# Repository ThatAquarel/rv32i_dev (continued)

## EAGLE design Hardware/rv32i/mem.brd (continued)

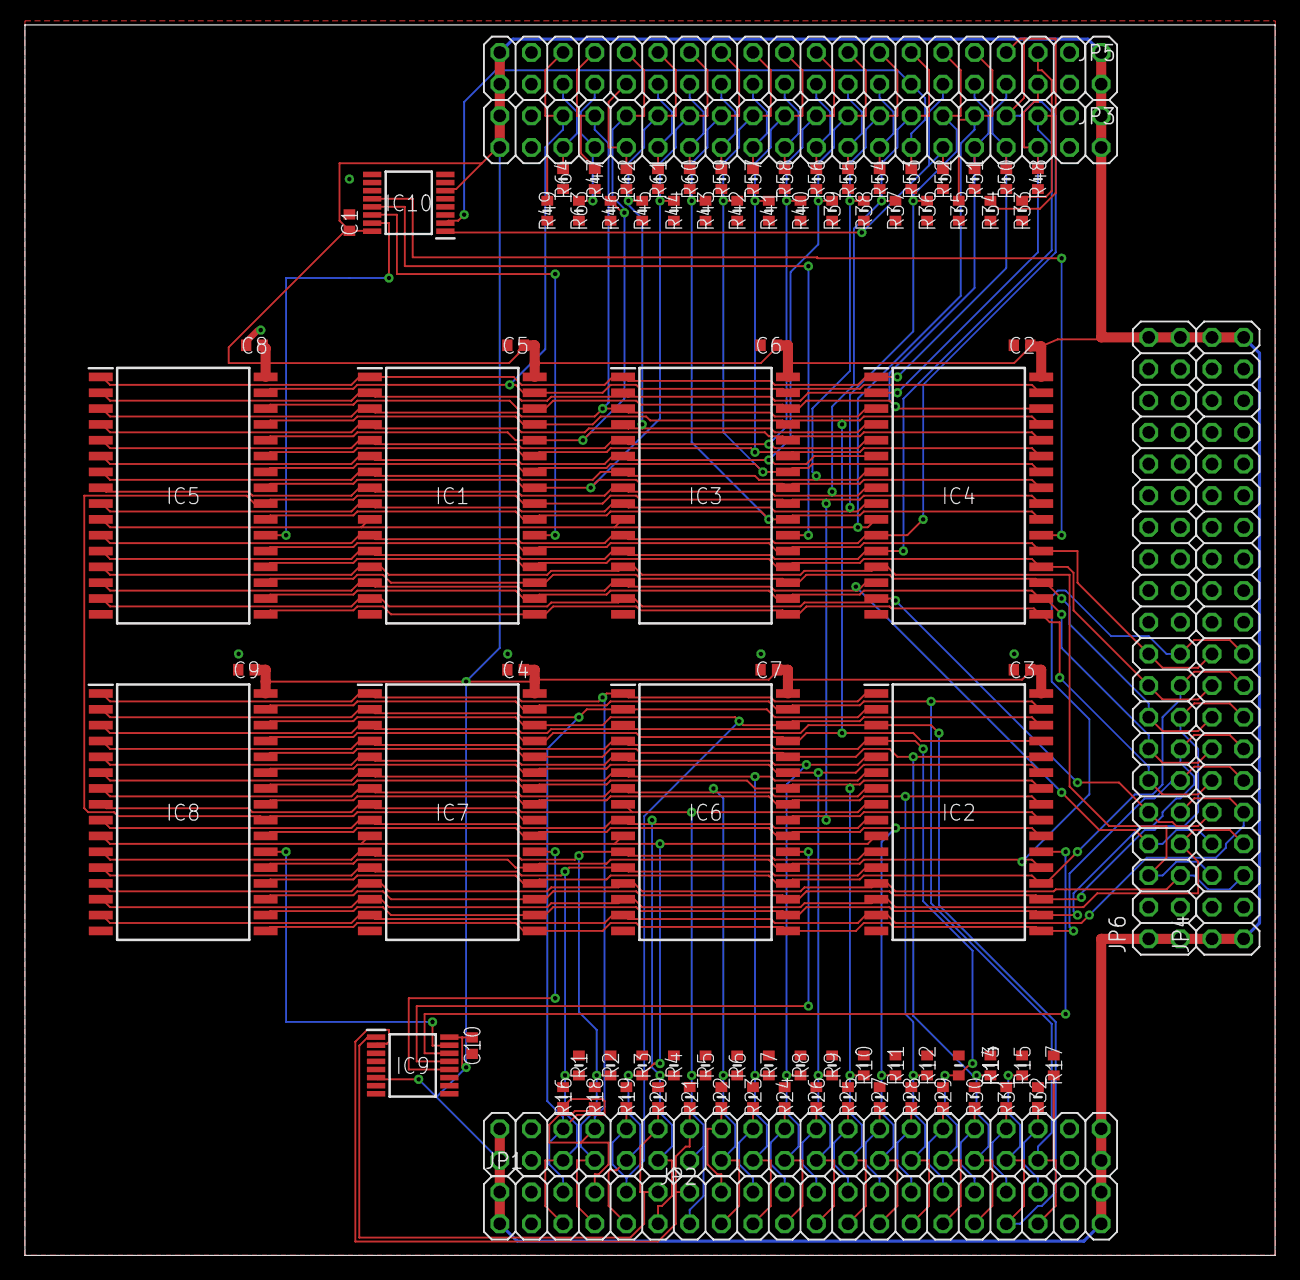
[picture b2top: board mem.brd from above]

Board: 2 copper layers, 100.3 x 98.7 mm, 90 parts (0 on the bottom side), 92 nets.

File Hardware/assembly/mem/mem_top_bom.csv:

Comment,Designator,Footprint,LCSC Part #
CC0603KRX7R9BB104,C1 C2 C3 C4 C5 C6 C7 C8 C9 C10,CAPC1608X90N,
IS61C5128AS-25QLI,IC1 IC2 IC3 IC4 IC5 IC6 IC7 IC8,SOIC127P1412X305-32N,
RC0603FR-0710KL,R1 R2 R3 R4 R5 R6 R7 R8 R9 R10 R11 R12 R13 R14 R15 R16 R17 R18 R19 R20 R21 R22 R23 R24 R25 R26 R27 R28 R29 R30 R31 R32 R33 R34 R35 R36 R37 R38 R39 R40 R41 R42 R43 R44 R45 R46 R47 R48 R49 R50 R51 R52 R53 R54 R55 R56 R57 R58 R59 R60 R61 R62 R63 R64,RESC1608X55N,
SN74HC138PWR,IC9 IC10,SOP65P640X120-16N,

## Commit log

2021-12-04 riscv ram + alu
    Added the Alu and Ram to the riscv simulation
2021-12-04 Compilation toolchain
2021-12-04 Updated Ram
    Better Ram
2021-12-04 Better Ram 2.0
    Updated Ram 2.0
2021-12-04 Add hex print
2021-12-04 Opcode decoder
2021-12-05 Add Notes
2021-12-05 Registers
    Added 6 registers
2021-12-05 32 reg
    Updated from 5 registers ro 32
2021-12-06 New Registers
    V2 Reg
2021-12-06 Added Zero-Reg and PC reg
    .
2021-12-09 Cpu structure
    Added the cpu
2021-12-10 R and I type instructions
    Added 2 sort of instructions
2021-12-11 ram bug
2021-12-17 Computer Almost Finished
2021-12-18 Add parts list
2021-12-21 Add eagle schematic
2021-12-21 Add multiplexer part
2021-12-22 Ram schematic
2021-12-22 Memory pcb layout
2021-12-23 Update memory schematic & parts
2021-12-23 Finish memory pcb & assembly files
2021-12-25 Add schmitt trigger to parts list
2021-12-26 Add register, counter, rom to parts list
2022-01-19 Implementation of Add/Sub
2022-01-22 Headers Changed
2022-01-22 ALU Headers & Timing Gates
2022-01-22 Rename ALU Header Pins
2022-01-22 Clock Gate
2022-01-22 Capacitors
2022-01-22 Resistors
2022-01-22 Alu design
2022-01-23 Modify ALU & Libraries
2022-01-23 Add FPGA Documents
2022-01-29 Add Altium Design Files
2022-02-05 Add new HX1K chip
2022-02-09 Finish Altium Design
2022-02-10 Some logic gates and testbench code added
2022-02-10 Pcb design & Orders
2022-02-10 Add .gitignore
2022-02-10 .gitignore & Order info
2022-02-10 Revert to previous board
2022-02-11 Add orders
2022-02-11 Add orders excel sheet
2022-02-11 Update .gitignore & totals
2022-02-27 Flash chip programming
2022-02-28 Working write cycle
2022-02-28 Full page writing
2022-03-03 Serial protocol
2022-03-03 Working flash chip programmer
2022-03-03 Change folder structure
2022-03-04 Verilog to bitstream compilation process
2022-03-04 All working
2022-03-05 Optimize flash chip programming
2025-01-07 docs
2025-01-07 add image
